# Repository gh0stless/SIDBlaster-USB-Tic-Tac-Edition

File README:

GNU GENERAL PUBLIC LICENSE

ftdi_template/   Template for FT_PROG, used to program USB-chip
pcb/             PCB design files
pic16f886/       Source code (MPASM) and compiled HEX for PIC16F886
win_hardsid_dll/ compiled windows hardsid driver (place in vice/acid64/sidplay/goatracker folder)

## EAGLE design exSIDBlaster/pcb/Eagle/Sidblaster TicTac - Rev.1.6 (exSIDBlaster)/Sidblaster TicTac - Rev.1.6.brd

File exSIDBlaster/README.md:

# exSIDBlaster - a farewell gift

If you want, you can now convert your SIDBlaster into half an exSID.

You may have heard of its near-perfect playback, even of problematic tunes.
The exSID project, started by **Thibaut Varène**, is a further development of the SIDBlaster circuit with truly sophisticated firmware. It was pretty much a Linux standalone product, but later, cross-platform support was offered, at least by JSIDPlay2.

Please also note that neither I nor Thibaut take responsibility for this hack, if YOU do it it is entirely your risk.

After the conversion, you essentially have an exSID but only one SID. You can use this in JSIDPlay2 or the web version. Simply enable "Fake Stereo" and the sound will always play. 

Please note that the exSID firmware is under a Creative Commons license, so I cannot offer you a conversion. Basically, you only need to break one wire and solder another as a bridge. Cut pin 7 of the PIC with a small flat side cutter (or perhaps nail clippers). 2.: Solder a jumper from PIC pin 15 to SID socket pin 5. Then flash the new firmware (hex file) and program the new template (make sure you choose the right one!). You can find out how to do this in the SIDBlaster assembly instructions and manual. 

Theoretically, a similar conversion might work with the SIDBlaster nano, but in practice I would advise against it: The smaller package size of the PIC might not be able to cope as well with the additional thermal load caused by the overclocking.

A hardsid.dll wrapper DLL for exSID is still in the works.

Andreas

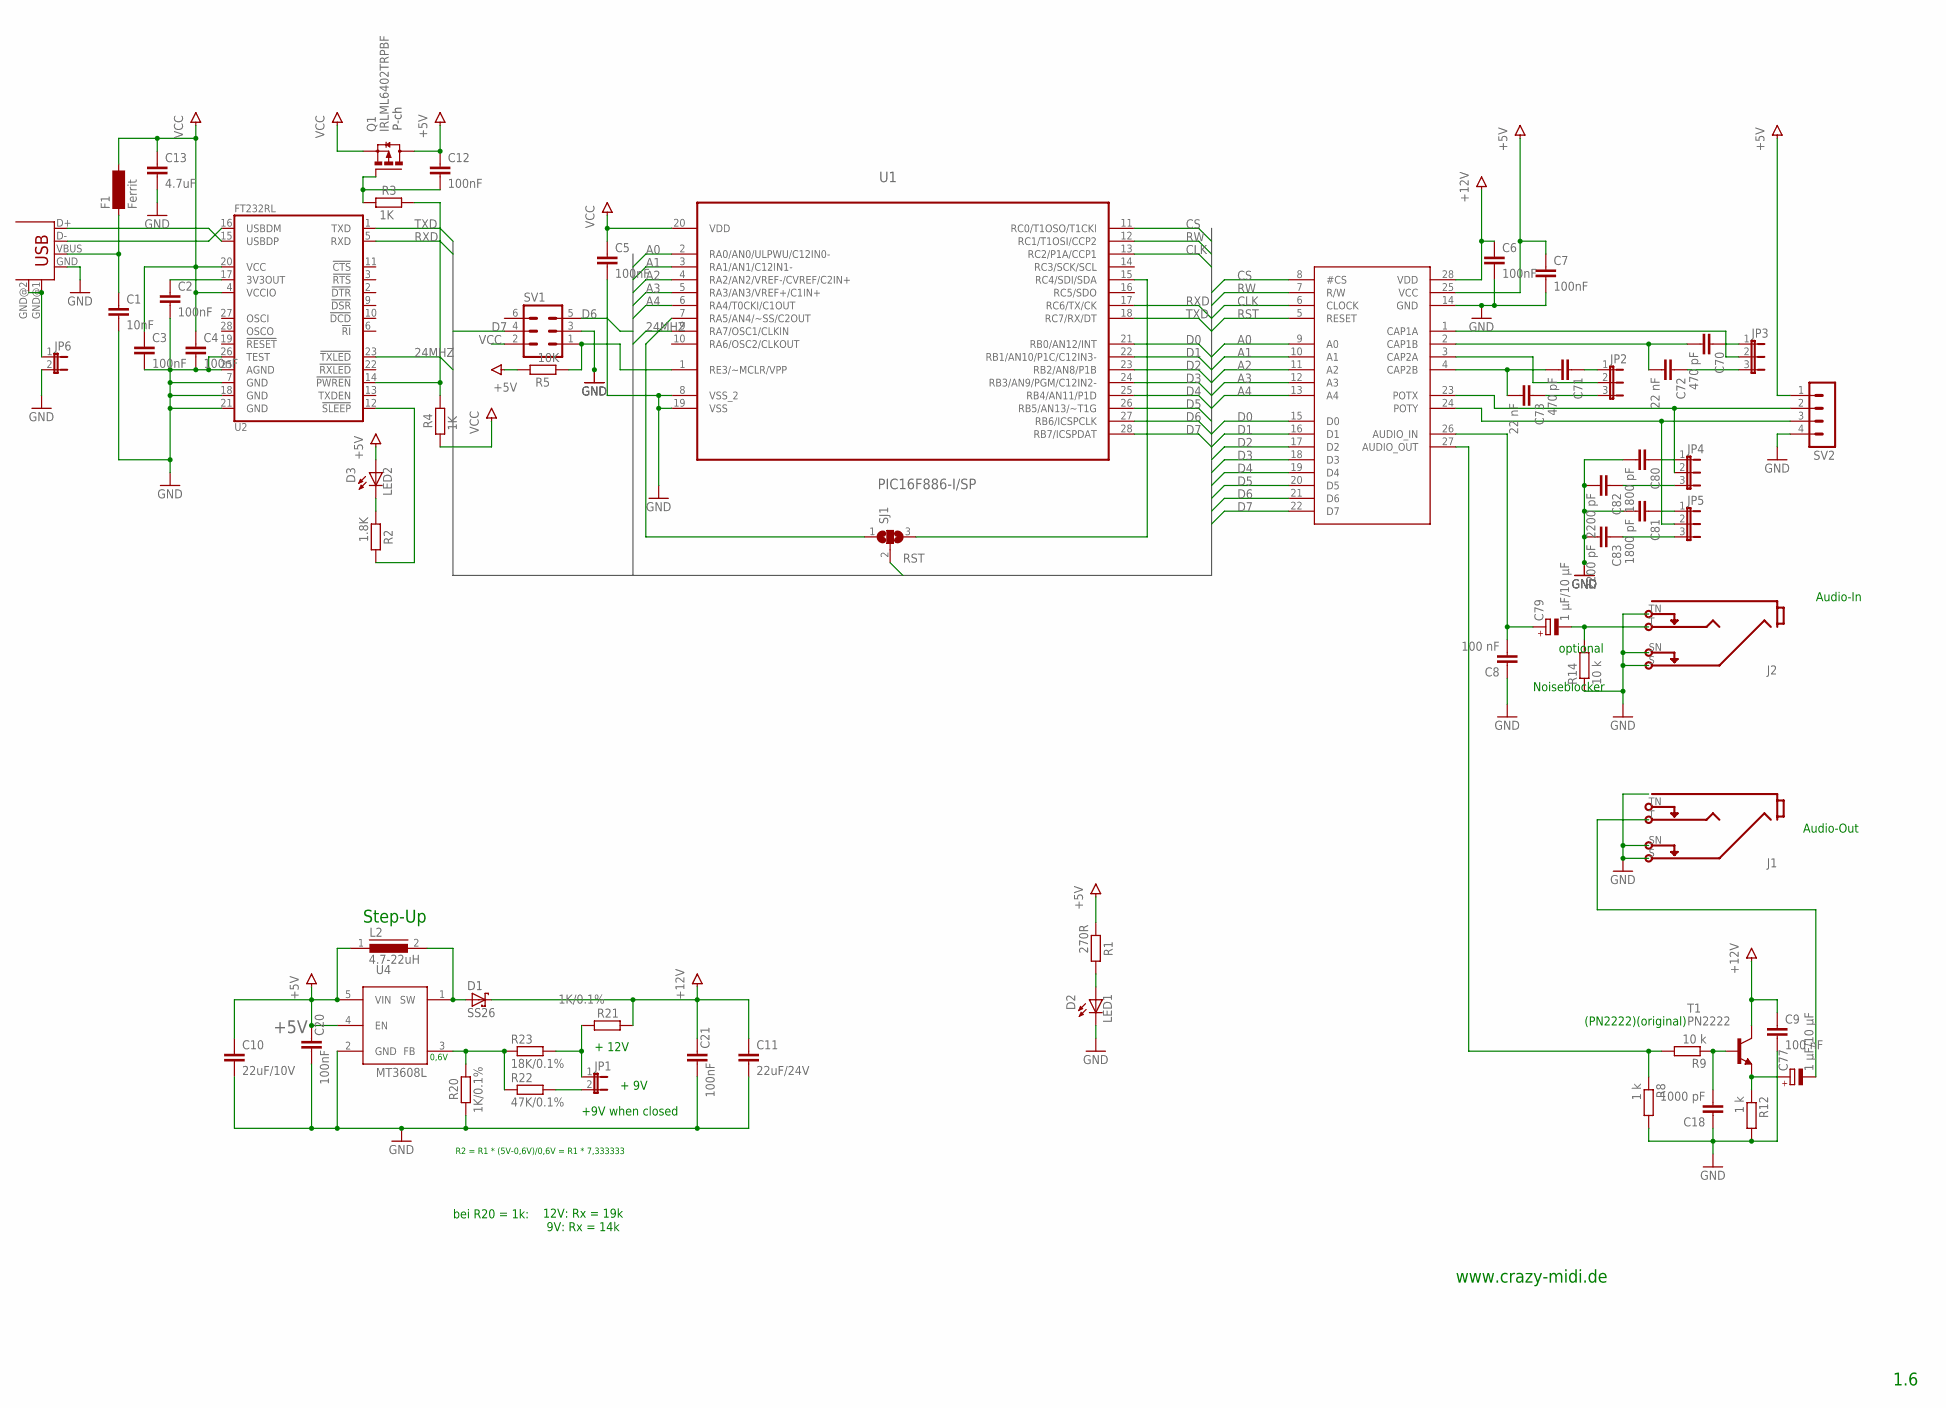
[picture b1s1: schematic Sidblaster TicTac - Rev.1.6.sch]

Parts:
C1: 10nF; C0805K
C2, C3, C4, C5, C6, C7, C12, C20, C21: 100nF; C0805K
C8, C9: 100 nF; C025-025X050
C10: 22uF/10V; C1206
C11: 22uF/24V; C1206
C13: 4.7uF; C1206
C18: 1000 pF; C025-025X050
C70, C71: 470 pF; C025-025X050
C72, C73: 22 nF; C025-025X050
C77, C79: 1 µF/10 µF; E2,5-5
C80, C81: 1800 pF; C025-025X050
C82, C83: 2200 pF; C025-025X050
D1: SS26; SMB
D2: LED1; CHIPLED_1206
D3: LED2; CHIPLED_1206
F1: Ferrit; SM-1206
J1, J2: MONOSW2; NEUTRIK-NRJ4HF
JP1, JP6: JP1E; JP1
JP2, JP3, JP4, JP5: JP2E; JP2
L2: 4.7-22uH; FPS
Q1: IRLML6402TRPBF; SOT23
R1: 270R; M0805
R2: 1.8K; M0805
R3, R4: 1K; M0805
R5: 10K; M0805
R8, R12: 1 k; 0207/10
R9, R14: 10 k; 0207/10
R20, R21: 1K/0.1%; M0805
R22: 47K/0.1%; M0805
R23: 18K/0.1%; M0805
SJ1: SJ2W; SJ_2
SV1: MA03-2
SV2: MA04-1
T1: PN2222; TO92
U1: PIC16F886-I/SP; DIP254P762X508-28
U2: FT232RL; SSOP28-LD
U3: 6581; DIL28-6
U4: MT3608L; SOT23-6
X1: USB-B-H

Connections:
24MHZ: U1.9 (RA7/OSC1/CLKIN), U2.23 (!TXLED)
+5V: C7.1, C10.1, C12.1, C20.2, D3.A, L2.1, Q1.3 (D), R1.2, R5.1, SV2.1, U3.25 (VCC), U4.4 (EN), U4.5 (VIN)
+12V: C6.1, C9.1, C11.1, C21.2, D1.C, R21.1, T1.3 (C), U3.28 (VDD)
A0: U1.2 (RA0/AN0/ULPWU/C12IN0-), U3.9 (A0)
A1: U1.3 (RA1/AN1/C12IN1-), U3.10 (A1)
A2: U1.4 (RA2/AN2/VREF-/CVREF/C2IN+), U3.11 (A2)
A3: U1.5 (RA3/AN3/VREF+/C1IN+), U3.12 (A3)
A4: U1.6 (RA4/T0CKI/C1OUT), U3.13 (A4)
C1: C2.1, U2.17 (3V3OUT)
CLK: U1.13 (RC2/P1A/CCP1), U3.6 (CLOCK)
CS: U1.11 (RC0/T1OSO/T1CKI), U3.8 (#CS)
D0: U1.21 (RB0/AN12/INT), U3.15 (D0)
D1: U1.22 (RB1/AN10/P1C/C12IN3-), U3.16 (D1)
D2: U1.23 (RB2/AN8/P1B), U3.17 (D2)
D3: U1.24 (RB3/AN9/PGM/C12IN2-), U3.18 (D3)
D4: U1.25 (RB4/AN11/P1D), U3.19 (D4)
D5: U1.26 (RB5/AN13/~T1G), U3.20 (D5)
D6: SV1.5, U1.27 (RB6/ICSPCLK), U3.21 (D6)
D7: SV1.4, U1.28 (RB7/ICSPDAT), U3.22 (D7)
GND: C1.2, C2.2, C3.2, C4.2, C5.2, C6.2, C7.2, C8.1, C9.2, C10.2, C11.2, C13.2, C18.1, C20.1, C21.1, C80.2, C81.2, C82.2, C83.2, D2.C, J1.S, J1.SN, J2.S, J2.SN, J2.TN, JP6.2, R8.2, R12.2, R14.1, R20.2, SV1.3, SV2.4, U1.8 (VSS_2), U1.19 (VSS), U2.7 (GND), U2.18 (GND), U2.21 (GND), U2.25 (AGND), U2.26 (TEST), U3.14 (GND), U4.2 (GND), X1.GND
unnamed: C8.2, C79.+, U3.26 (AUDIO_IN)
unnamed: U2.15 (USBDP), X1.D+
unnamed: C79.-, J2.T, R14.2
unnamed: C71.1, JP2.1
unnamed: R8.1, R9.2, U3.27 (AUDIO_OUT)
unnamed: JP1.1, R21.2, R23.2
unnamed: C71.2, C73.2, U3.4 (CAP2B)
unnamed: C73.1, JP2.3
unnamed: JP2.2, U3.3 (CAP2A)
unnamed: C70.2, C72.2, U3.2 (CAP1B)
unnamed: C70.1, JP3.1
unnamed: C72.1, JP3.3
unnamed: JP3.2, U3.1 (CAP1A)
unnamed: JP4.2, SV2.2, U3.23 (POTX)
unnamed: U2.16 (USBDM), X1.D-
unnamed: R5.2, SV1.1, U1.1 (RE3/~MCLR/VPP)
unnamed: JP5.2, SV2.3, U3.24 (POTY)
unnamed: C77.-, J1.T
unnamed: C18.2, R9.1, T1.2 (B)
unnamed: C77.+, R12.1, T1.1 (E)
unnamed: D1.A, L2.2, U4.1 (SW)
unnamed: JP1.2, R22.2
unnamed: D2.A, R1.1
unnamed: D3.C, R2.2
unnamed: C1.1, F1.1, X1.VBUS
unnamed: C80.1, JP4.1
unnamed: C82.1, JP4.3
unnamed: R2.1, U2.12 (!SLEEP)
unnamed: JP6.1, X1.GND@1 (GND), X1.GND@2 (GND)
unnamed: C81.1, JP5.1
unnamed: C83.1, JP5.3
unnamed: C12.2, Q1.1 (G), R3.2
unnamed: SJ1.3, U1.15 (RC4/SDI/SDA)
unnamed: R3.1, R4.1, U2.14 (!PWREN)
unnamed: SJ1.1, U1.7 (RA5/AN4/~SS/C2OUT)
R22: R20.1, R22.1, R23.1, U4.3 (FB)
RST: SJ1.2, U3.5 (RESET)
RW: U1.12 (RC1/T1OSI/CCP2), U3.7 (R/W)
RXD: U1.17 (RC6/TX/CK), U2.5 (RXD)
TXD: U1.18 (RC7/RX/DT), U2.1 (TXD)
VCC: C3.1, C4.1, C5.1, C13.1, F1.2, Q1.2 (S), R4.2, SV1.2, U1.20 (VDD), U2.4 (VCCIO), U2.20 (VCC)

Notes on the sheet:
Audio-Out
Audio-In
Noiseblocker
optional
(PN2222)(original)
Step-Up
0,6V
R2 = R1 * (5V-0,6V)/0,6V = R1 * 7,333333
+ 9V
+ 12V
bei R20 = 1k:
12V: Rx = 19k 9V: Rx = 14k
+9V when closed
1.6
www.crazy-midi.de
P-ch

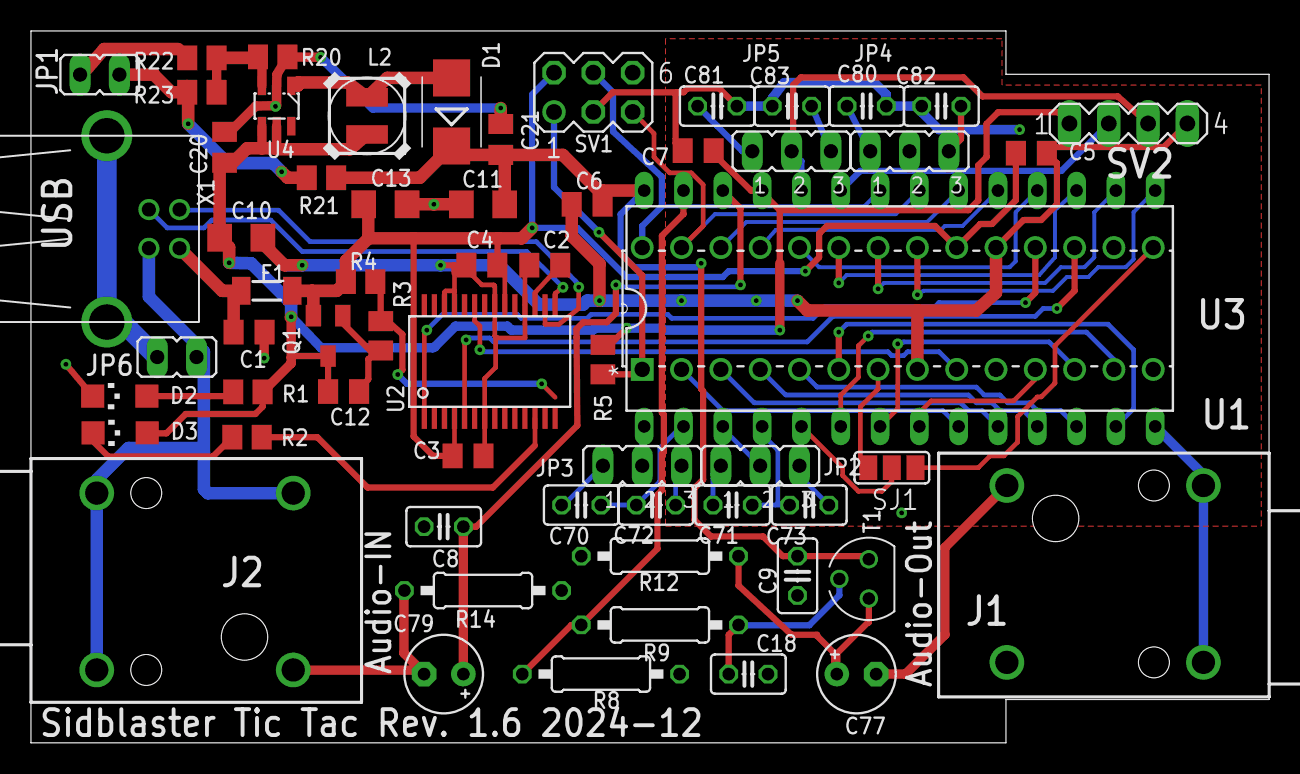
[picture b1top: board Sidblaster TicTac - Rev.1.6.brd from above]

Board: 2 copper layers, 80.0 x 46.0 mm, 62 parts (0 on the bottom side), 61 nets.

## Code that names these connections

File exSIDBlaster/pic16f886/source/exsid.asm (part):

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#define	SIDDAT		PORTB		; SID bus data port
#define	SIDDDR		TRISB		; SID bus data direction

#define	EXTCLK		RA7

#if HWVERS == "C"
 #define	CTLCS1		RC0
 #define	CTL_RW		RC1
 #define	CTLCS0		RC3
 #define	CTLRST		RC4
#else	; not "C"
 #if HWVERS == "B"
  #define	CTL_RW		RC0		; SID R/W on SIDCTL
  #define	CTLCS0		RC1		; SID CS0 (6581) on SIDCTL
 #else ; "A"
  #define	CTLCS0		RC0		; SID CS0 (6581) on SIDCTL
  #define	CTL_RW		RC1		; SID R/W on SIDCTL
 #endif	; HWVERS == "B"
 #define	CTLRST		RC3		; SID RST on SIDCTL
 #define	CTLCS1		RC5		; SID CS1 (8580) on SIDCTL
#endif	; HWVERS == "C"
#define	CTLCLK		RC2		; SID CLK on SIDCTL
#define	FTDIRX		RC6
#define	FTDITX		RC7
	
; By default RW is held low. The read routine must bring it back low after exec.
; Chip select bitmask.
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	;CCP1CON = 0b00001100 ;

	BANKSEL	TRISC		; BANK 1
	BCF	TRISC, RC2	; Make sure pin is an output
	MOVLW	B'00000101'
	MOVWF	PR2
	
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
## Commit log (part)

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2017-05-01 Orderlist (Reichelt.de)
    Orderlist for the Parts
2017-08-21 Create dummy
2017-08-21 a kind of manual...
2018-03-02 Rev. 1.2 uploaded
2018-03-02 Update Firmware
2018-03-02 Updated Firmware
2018-03-07 Updated crib sheet
2018-07-17 add Assembly instructions
2018-10-11 Added wiring Pic3 SV1
2018-10-11 added photo
2018-10-12 Added FAQ with wiring Pic for Programming
    * Added wiring Pic3 SV1
    * added photo
2018-12-13 Updated Aufbauanleitung
2019-01-04 Updated Doc
2019-08-01 kleine Aenderung
2020-05-09 add readme
2020-05-23 Update Documentation
2020-08-17 updated docs
2020-08-17 updated hardsid.dll
2021-02-05 add latest hardsid.dll beta
2021-02-10 (re)replaced withe the original dll from 2015
2021-02-11 upload new beta of dll
2021-04-20 linux/mac port binarys added
2021-05-22 Rev1.3 PCB added
2021-05-22 fix for readme
2021-05-22 fix readme
2021-05-23 Rev.1.3 small fix
2021-06-11 The 1.3 release
2021-06-16 The Rev. 1.3 release
2021-09-28 Usermanual updated
2022-05-05 Rev. 1.4
2022-06-06 documentation updated
2022-07-06 Rev. 1.5
2022-08-01 Add 3D-printed case (#3)
    * Add files via upload
    * Delete SIDBlaster-USB-Tic-Tac-Case-Top-V1.stl
    * Create README.md
    * Add files via upload
    * Update README.md
2022-09-23 PCB Rev.1.5
2022-10-19 documantation update/rev.1.5 pcb
2022-10-19 doc updated
2022-10-19 Updated BOM
2023-01-02 Update Assembly Instructions
2023-01-04 a bug in handbuch
2023-06-25 add MacOS Universal Binary (M1/M2)
2024-10-31 Halloween 2024 Upload Production files
2024-11-12 Fix Manual
2024-11-23 Update Manual
2025-02-01 fix2
2025-07-05 exSIDBlaster
2025-08-27 updated manual
2025-10-09 ein Tipfehler im Handbuch
2025-10-09 corrected

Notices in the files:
exSIDBlaster/pic16f886/source/exsid.asm:
(C) 2015-2016 T. Varene
License: CC BY-NC-SA 4.0
